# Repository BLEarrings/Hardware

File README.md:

# BLEarrings Hardware 

## Description
This repository contains the files for a custom project including a KiCad PCB design, a custom KiCad parts library, and a Blender-modeled enclosure.

## Contents
- **KiCad PCB Design (in PCB)**: The PCB design files for the project.
- **Custom KiCad Parts Library (in EasyEDA2kiCAD)**: A library of custom parts used in the PCB design.
- **Blender Modeled Enclosure (in CAD)**: 3D models of the enclosure designed in Blender.

## Getting Started
1. **Install KiCad**: Download and install KiCad from the official website.
2. **Install Blender**: Download and install Blender from the official website.
3. **Open the Project**: Open the KiCad project files in KiCad and the Blender files in Blender.

## Usage
- **KiCad PCB Design**: Use KiCad to view and modify the PCB design or checkout the [V1 Schematic](https://github.com/BLEarrings/Hardware/blob/main/PCB/Schematics/BLEEarringsV1.pdf).
- **Custom KiCad Parts Library EASYEDA2KICAD**: Use the custom parts library (easyeda2kicad) in your KiCad projects.
- **Blender Modeled Enclosure**: Use Blender to view and modify the enclosure design or use the provided STL to print one yourself.

## License
This project is licensed under the MIT License - see the `LICENSE` file for details.

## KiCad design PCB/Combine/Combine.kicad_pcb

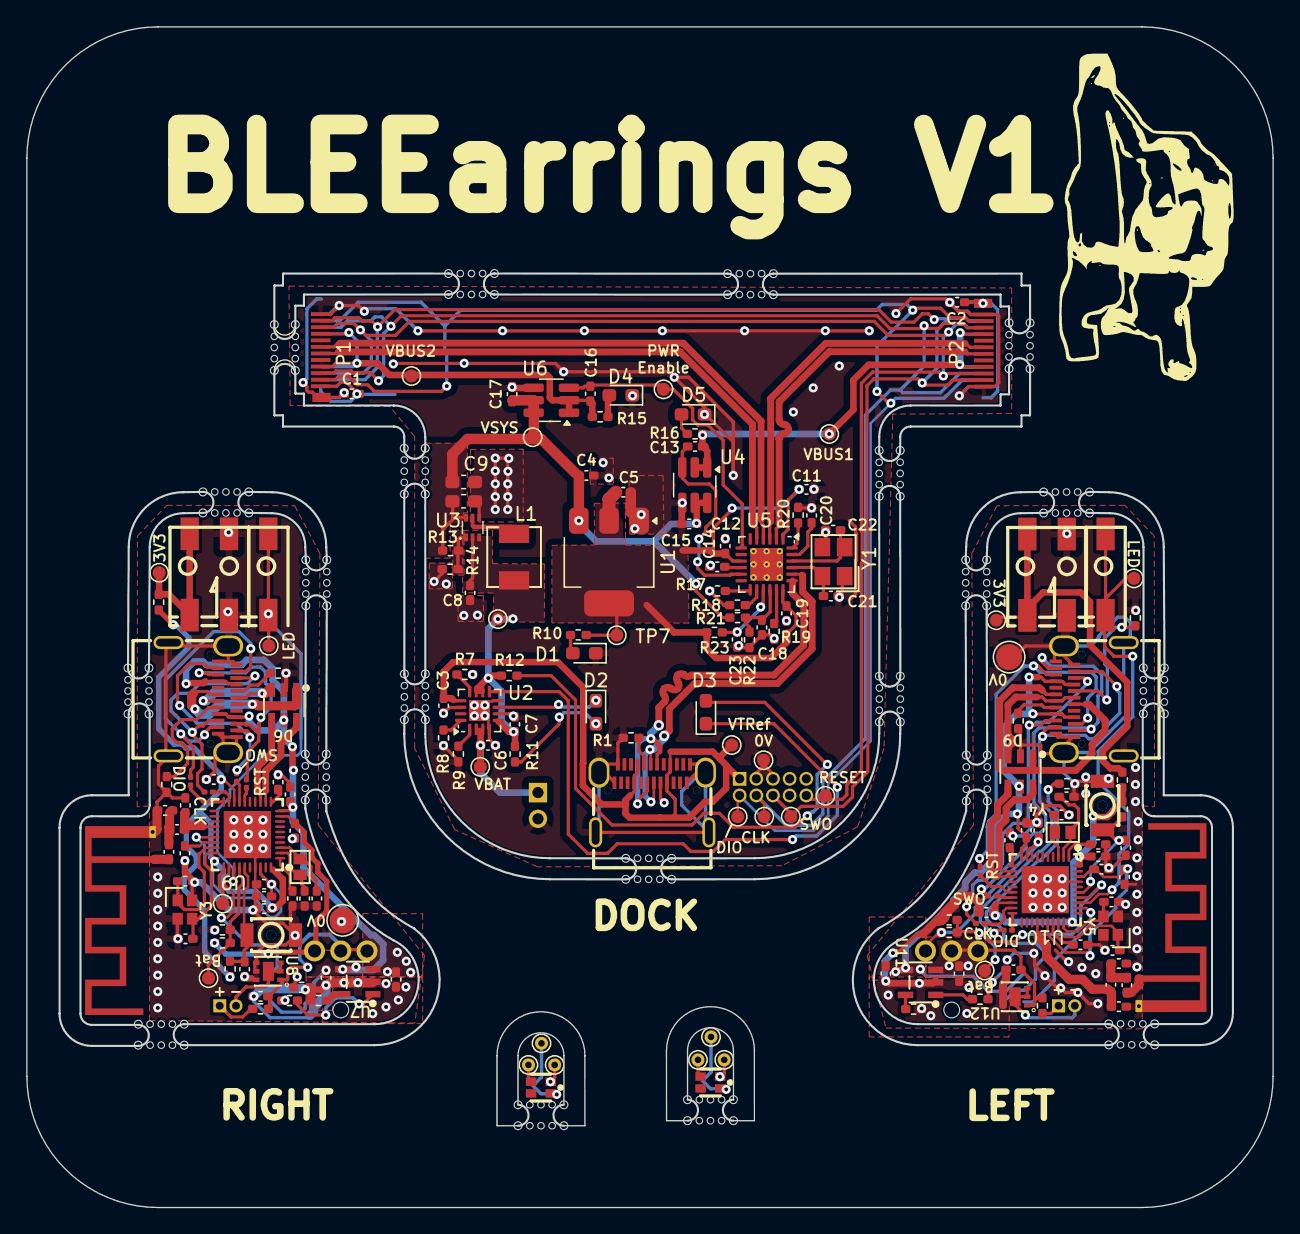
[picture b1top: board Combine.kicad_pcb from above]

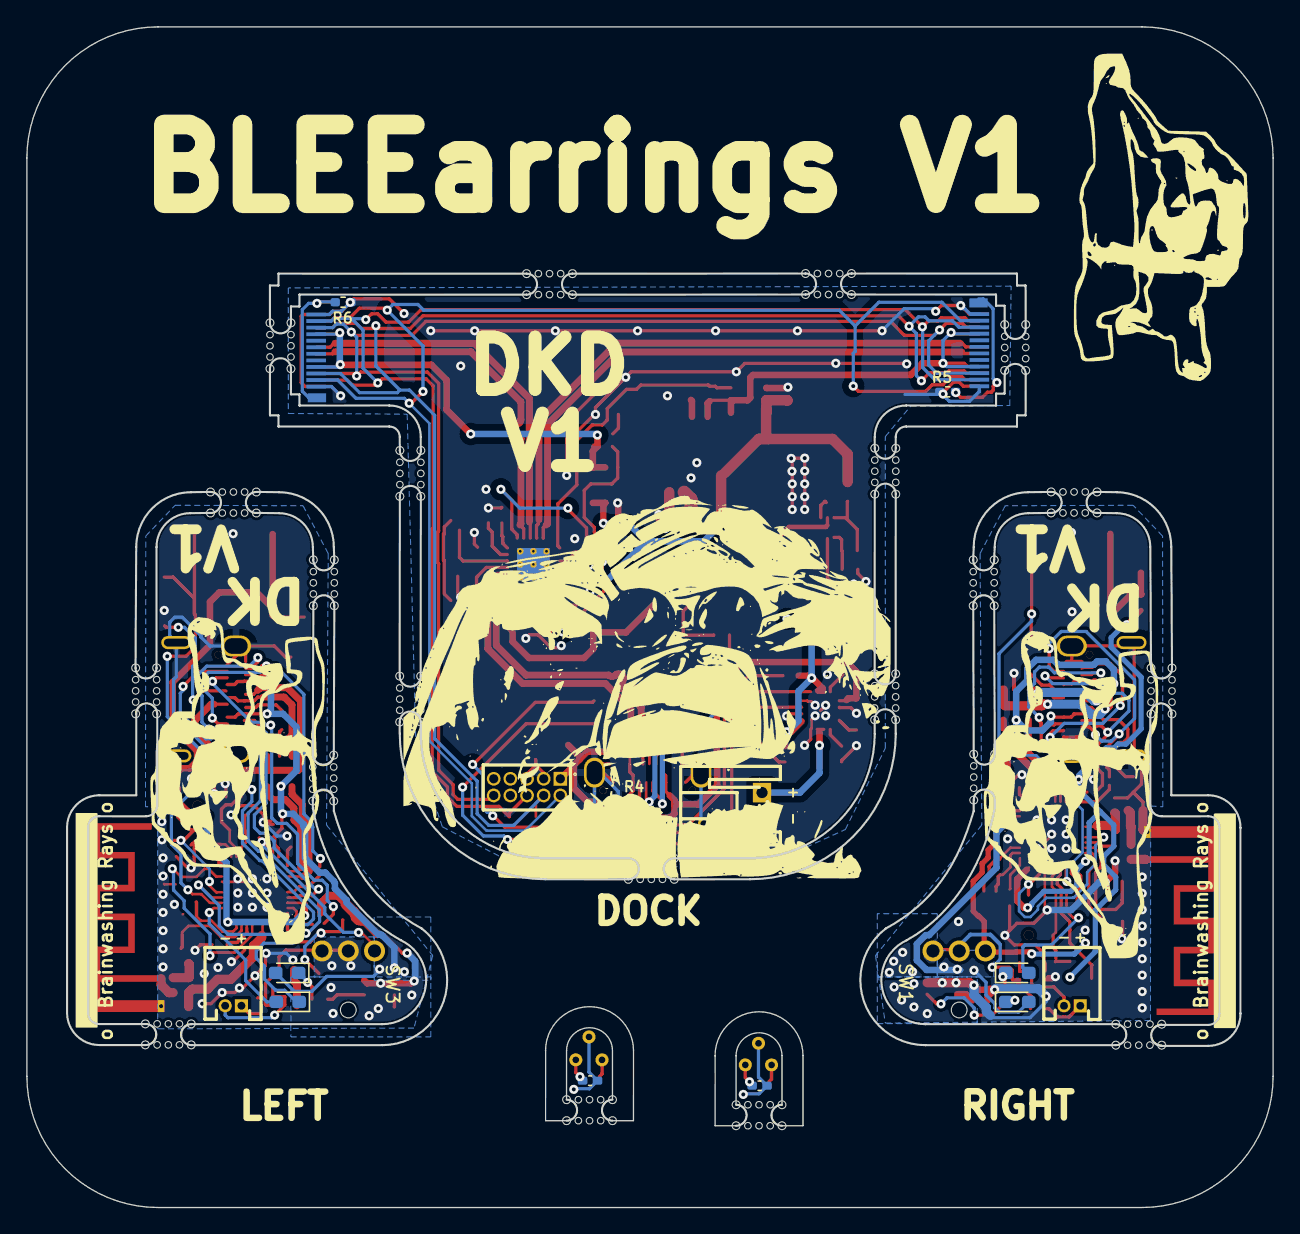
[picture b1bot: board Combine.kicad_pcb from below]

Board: 2 copper layers, 95.0 x 90.0 mm, 194 parts (15 on the bottom side), 135 nets.

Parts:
ANT1, ANT2: Texas_SWRA117D_2.4GHz_Left
BT1: Battery Pimoroni 1200mAh; CONN-TH_S2B-PH-K-S-LF-SN
BT2, BT3: Battery Gens ace 200mAh 1S 45C 3.7V; CONN-TH_530480210
C1, C2, C11, C13, C16, C18, C19, C20, C25, C30, C33, C41, C46, C49, C57, C60, C63, C64: 100n; C_0402_1005Metric_Pad0.74x0.62mm_HandSolder
C3, C12, C14, C23, C34, C38, C50, C54: 1u; C_0402_1005Metric_Pad0.74x0.62mm_HandSolder
C4, C5: 2.2u; C_0402_1005Metric_Pad0.74x0.62mm_HandSolder
C6, C7, C15, C17, C28, C29, C31, C44, C45, C47: 4.7u; C_0402_1005Metric_Pad0.74x0.62mm_HandSolder
C8, C24, C26, C59, C61: 10u; C_0402_1005Metric_Pad0.74x0.62mm_HandSolder
C9, C10: 22u; C_0603_1608Metric_Pad1.08x0.95mm_HandSolder
C21, C22: 18p; C_0402_1005Metric_Pad0.74x0.62mm_HandSolder
C27, C32, C43, C48: 8p; C_0402_1005Metric_Pad0.74x0.62mm_HandSolder
C35, C51: 1p; C_0402_1005Metric_Pad0.74x0.62mm_HandSolder
C36, C52: 100p; C_0402_1005Metric_Pad0.74x0.62mm_HandSolder
C37, C53: 1.2p; C_0402_1005Metric_Pad0.74x0.62mm_HandSolder
C39, C55: NC; C_0402_1005Metric_Pad0.74x0.62mm_HandSolder
C40, C42, C56, C58: 12p; C_0402_1005Metric_Pad0.74x0.62mm_HandSolder
D1: LED; LED_0603_1608Metric_Pad1.05x0.95mm_HandSolder
D2: BLUE RED; LED_0603_1608Metric_Pad1.05x0.95mm_HandSolder
D3, D4, D5, D8, D10: BLUE LED; LED_0603_1608Metric_Pad1.05x0.95mm_HandSolder
D6, D9: USBLC6-2SC6_C2687116; SOT-23-6_L2.9-W1.6-P0.95-LS2.8-BL
D7, D11: RED LED; LED_0603_1608Metric_Pad1.05x0.95mm_HandSolder
D12, D13: 2758; LED-SMD_4P-L1.6-W1.5_XL-1615RGBC-WS2812B
J1, J3, J6: USB_C_Receptacle; TYPE-C-SMD_C9900025773
J2: Conn_01x10_Socket; HDR-TH_10P-P1.27-V-M-R2-C5-S1.27-1
J4, J7: Screw_Terminal_01x01; CONN-SMD_custom1
J5, J8: Screw_Terminal_01x02; CONN-SMD_2059-302
L1: 4.7u; IND-SMD_L4.5-W4.1
L2, L4: 4.7n; L_0402_1005Metric_Pad0.77x0.64mm_HandSolder
L3, L5: 2.2n; L_0402_1005Metric_Pad0.77x0.64mm_HandSolder
P1, P2: USB_C_Plug; USB-C-SMD_TYPE-C-24P-GTJB-040
R1, R4, R24, R25, R38, R39: 5k1; R_0402_1005Metric_Pad0.72x0.64mm_HandSolder
R5, R6, R11, R12: 1k; R_0402_1005Metric_Pad0.72x0.64mm_HandSolder
R7: 1.18k; R_0402_1005Metric_Pad0.72x0.64mm_HandSolder
R8: 1.78k; R_0402_1005Metric_Pad0.72x0.64mm_HandSolder
R9, R21, R22, R23: 10k; R_0402_1005Metric_Pad0.72x0.64mm_HandSolder
R10, R26, R37, R48, R49: 2k; R_0402_1005Metric_Pad0.72x0.64mm_HandSolder
R13: 732; R_0402_1005Metric_Pad0.72x0.64mm_HandSolder
R14, R34, R45: 100k; R_0402_1005Metric_Pad0.72x0.64mm_HandSolder
R15, R16, R29, R40: 220; R_0402_1005Metric_Pad0.72x0.64mm_HandSolder
R17, R18, R19, R28, R51: 100; R_0402_1005Metric_Pad0.72x0.64mm_HandSolder
R20: 12k; R_0402_1005Metric_Pad0.72x0.64mm_HandSolder
R27, R50: 4k99; R_0402_1005Metric_Pad0.72x0.64mm_HandSolder
R30, R31, R32, R33, R41, R42, R43, R44: NF; R_0201_0603Metric
R35, R46: 33k; R_0402_1005Metric_Pad0.72x0.64mm_HandSolder
R36, R47: 470; R_0402_1005Metric_Pad0.72x0.64mm_HandSolder
SW1, SW3: TK-6580B-1; SW-TH_TK-6580B-1
SW2, SW4: SW_DIP_x01; KEY-SMD_L3.0-W2.5-LS4.0
TP1, TP2, TP3, TP4, TP5, TP6, TP7, TP8, TP9, TP10, TP11, TP12, TP13, TP14, TP15, TP17, TP18, TP19, TP28: TestPoint; TestPoint_Pad_D1.0mm
TP16, TP20: TestPoint; TestPoint_Pad_D2.0mm
TP21, TP22, TP23, TP24, TP25, TP26: TestPoint; TestPoint_THTPad_D1.0mm_Drill0.5mm
TPL3: TestPoint; TestPoint_Pad_D1.0mm
U1: AMS1117-3.3; SOT-223-3_TabPin2
U2: BQ24073RGT; VQFN-16-1EP_3x3mm_P0.5mm_EP1.6x1.6mm
U3: TPS61023DRLR; SOT-563_L1.6-W1.2-P0.50-LS1.6-BR
U4, U6: SIP32509DT-T1-GE3; SOT-23-6_Handsoldering
U5: USB2422T-I/MJ; HVQFN-24-1EP_4x4mm_P0.5mm_EP2.5x2.5mm_ThermalVias
U7, U11: MCP73831T-2ACI/OT; SOT-23-5_L3.0-W1.7-P0.95-LS2.8-BL
U8, U12: XB6096I2SV; WDFN-6_L2.0-W2.0-P0.65-BL-EP
U9, U10: NRF52833-QDAA-R7; QFN-40_L5.0-W5.0-P0.40-TL-EP3.6
Y1: X322524MOB4SI; CRYSTAL-SMD_4P-L3.2-W2.5-BL
Y2, Y4: X161032768KLD2SI; CRYSTAL-SMD_L1.6-W1.0
Y3, Y5: XL7EL89CKI-111YLC-32M; CRYSTAL-SMD_4P-L2.0-W1.6-BL

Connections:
+3V3_1: C5.1, C11.2, C12.2, C19.2, R10.2, R23.2, TP7.1, U1.2 (VO), U5.1 (VDD33), U5.9 (VDD33), U5.18 (VDD33)
+3V3_2: C30.1, C34.2, R36.2, R37.2, U9.18 (VDD), U9.30 (VDD), U9.40 (VDD)
+3V3_3: C46.1, C50.2, R47.2, R48.2, U10.18 (VDD), U10.30 (VDD), U10.40 (VDD)
+BATT_1: C28.2, R34.2, SW1.3, U9.9 (VDDH)
+BATT_2: C44.2, R45.2, SW3.3, U10.9 (VDDH)
/Dock/DeviceSelect/D+: J1.A6 (D+), J1.B6 (D+), U5.20 (USBDP_UP)
/Dock/DeviceSelect/D-: J1.A7 (D-), J1.B7 (D-), U5.19 (USBDM_UP)
/Dock/DeviceSelect/D_1+: P2.A6 (D+), U5.3 (USBDP_DN1/PRT_DIS_P1)
/Dock/DeviceSelect/D_1-: P2.A7 (D-), U5.2 (USBDM_DN1/PRT_DIS_M1)
/Dock/DeviceSelect/D_2+: P1.A6 (D+), U5.5 (USBDP_DN2/PRT_DIS_P2)
/Dock/DeviceSelect/D_2-: P1.A7 (D-), U5.4 (USBDM_DN2/PRT_DIS_M2)
/Dock/DeviceSelect/VBUS1: C13.2, P2.A4 (VBUS), P2.A9 (VBUS), P2.B4 (VBUS), P2.B9 (VBUS), R16.1, TP11.1, U4.1 (OUT), U4.2 (OUT)
/Dock/DeviceSelect/VBUS2: C16.2, P1.A4 (VBUS), P1.A9 (VBUS), P1.B4 (VBUS), P1.B9 (VBUS), R15.1, TP12.1, U6.1 (OUT), U6.2 (OUT)
/Dock/DeviceSelect/Vsys: C4.1, C9.1, C10.1, C15.2, C17.2, R13.2, R21.2, TP10.1, U1.3 (VI), U3.6 (VOUT), U4.5 (IN), U4.6 (IN), U6.5 (IN), U6.6 (IN)
/Dock/ExtraBattery/3.7Out: C7.1, C8.1, L1.1, R11.2, R12.2, TP9.1, U2.5 (EN2), U2.10 (OUT), U2.11 (OUT), U3.2 (EN), U3.3 (VIN)
/Dock/ExtraBattery/FB: R13.1, R14.2, U3.1 (FB)
/Dock/ExtraBattery/VBAT: BT1.1 (+), C6.1, TP8.1, U2.2 (BAT), U2.3 (BAT)
/EarringL/DSP/VBUS: C45.2, C61.1, D9.5 (VBUS), D11.2 (A), J6.A4 (VBUS), U10.10 (VBUS), U11.4 (VDD)
/EarringL/DSP/nReset: J6.A10 (RX2-), J6.B10 (RX1-), R43.1
/EarringL/LUSBd+: D9.3 (I/O2), J6.A6 (D+), J6.B6 (D+)
/EarringL/LUSBd-: D9.1 (I/O1), J6.A7 (D-), J6.B7 (D-)
/EarringL/Power/VBAT: C59.1, C60.1, R51.2, SW3.1, SW3.2, U11.3 (VBAT), U12.1 (VDD)
/EarringR/DSP/VBUS: C26.1, C29.2, D6.5 (VBUS), D7.2 (A), J3.A4 (VBUS), U7.4 (VDD), U9.10 (VBUS)
/EarringR/DSP/nReset: J3.A10 (RX2-), J3.B10 (RX1-), R32.1
/EarringR/Power/VBAT: C24.1, C25.1, R28.2, SW1.1, SW1.2, U7.3 (VBAT), U8.1 (VDD)
BatRef_1: R34.1, R35.2, TP13.1, U9.34 (P0.29_AIN5)
BatRef_2: R45.1, R46.2, TP17.1, U10.34 (P0.29_AIN5)
D1+: D6.4 (I/O2), U9.13 (D+)
D1-: D6.6 (I/O1), U9.12 (D-)
D2+: D9.4 (I/O2), U10.13 (D+)
D2-: D9.6 (I/O1), U10.12 (D-)
DEC6_1: C38.1, C39.1, U9.26 (DEC6), U9.38 (DEC4)
DEC6_2: C54.1, C55.1, U10.26 (DEC6), U10.38 (DEC4)
GND1: BT1.2 (-), C1.1, C2.1, C3.2, C4.2, C5.2, C6.2, C7.2, C8.2, C9.2, C10.2, C11.1, C12.1, C14.1, C15.1, C17.1, C18.1, C19.1, C20.1, C21.2, C22.1, C23.1, D1.1 (K), D4.1 (K), D5.1 (K), J1.A1 (GND), J1.S1 (SHIELD), J2.3, J2.5, P1.A1 (GND), P2.A1 (GND), R1.1, R4.1, R5.2, R6.2, R7.2, R8.2, R9.1, R14.1, R17.1, R18.1, R19.1, R20.1, R22.1, TP1.1, U1.1 (GND), U2.4 (~CE), U2.6 (EN1), U2.8 (VSS), U2.14 (TMR), U2.17 (VSS), U3.4 (GND), U4.4 (GND), U5.25 (EP), U6.4 (GND), Y1.1, Y1.3
GND2: ANT1.2 (GND), C24.2, C25.2, C26.2, C27.1, C28.1, C29.1, C30.2, C31.1, C32.1, C33.1, C34.1, C35.2, C36.2, C37.2, C38.2, C39.2, C40.1, C41.1, C42.1, D6.2 (GND), J3.A1 (GND), J3.S1 (SHIELD), J5.2, R24.1, R25.1, R27.2, R29.1, R35.1, SW2.2, TP16.1, U7.2 (VSS), U8.4 (VM), U8.5 (VM), U8.6 (VM), U9.37 (VSS), U9.41 (VSS), Y3.2, Y3.3
GND3: ANT2.2 (GND), C43.1, C44.1, C45.1, C46.2, C47.1, C48.1, C49.1, C50.1, C51.2, C52.2, C53.2, C54.2, C55.2, C56.1, C57.1, C58.1, C59.2, C60.2, C61.2, D9.2 (GND), J6.A1 (GND), J6.S1 (SHIELD), J8.2, R38.1, R39.1, R40.1, R46.1, R50.2, SW4.2, TP20.1, U10.37 (VSS), U10.41 (VSS), U11.2 (VSS), U12.4 (VM), U12.5 (VM), U12.6 (VM), Y5.2, Y5.3
LED_A_1: D8.2 (A), U9.32 (P0.02_AIN0)
LED_A_2: D10.2 (A), U10.32 (P0.02_AIN0)
NEO_LED_1: J4.1, TP14.1, U9.33 (P0.28_AIN4)
NEO_LED_2: J7.1, TP18.1, U10.33 (P0.28_AIN4)
unnamed: ANT1.1 (FP), L3.2
unnamed: ANT2.1 (FP), L5.2
unnamed: BT2.1 (+), R28.1
unnamed: BT2.2 (-), U8.2 (GND), U8.3 (GND), U8.7 (EP)
unnamed: BT3.1 (+), R51.1
unnamed: BT3.2 (-), U12.2 (GND), U12.3 (GND), U12.7 (EP)
unnamed: C37.1, L2.2, L3.1
unnamed: C53.1, L4.2, L5.1
unnamed: D1.2 (A), R10.1
unnamed: D2.2 (A), R11.1
unnamed: D2.1 (K), U2.7 (~PGOOD)
unnamed: D3.2 (A), R12.1
unnamed: D3.1 (K), U2.9 (~CHG)
unnamed: D4.2 (A), R15.2
unnamed: D5.2 (A), R16.2
unnamed: D6.1 (I/O1), J3.A7 (D-), J3.B7 (D-)
unnamed: D6.3 (I/O2), J3.A6 (D+), J3.B6 (D+)
unnamed: D7.1 (K), R26.1
unnamed: D8.1 (K), R29.2
unnamed: D10.1 (K), R40.2
unnamed: D11.1 (K), R49.1
unnamed: D12.4 (DIN), TP21.1
unnamed: C63.2, D12.1 (VDD), TP22.1
unnamed: C63.1, D12.3 (VSS), TP23.1
unnamed: D13.4 (DIN), TP24.1
unnamed: C64.2, D13.1 (VDD), TP25.1
unnamed: C64.1, D13.3 (VSS), TP26.1
unnamed: J1.A5 (CC1), R1.2
unnamed: J1.B5 (CC2), R4.2
unnamed: J3.A5 (CC1), R24.2
unnamed: J3.B5 (CC2), R25.2
unnamed: J5.1, R36.1, TP15.1
unnamed: J6.A5 (CC1), R38.2
unnamed: J6.B5 (CC2), R39.2
unnamed: J8.1, R47.1, TP19.1
unnamed: C1.2, P1.S1 (SHIELD), R5.1
unnamed: C2.2, P2.S1 (SHIELD), R6.1
unnamed: R7.1, U2.12 (ILIM)
unnamed: R8.1, U2.16 (ISET)
unnamed: R9.2, U2.1 (TS)
unnamed: L1.2, U3.5 (SW)
unnamed: C14.2, U5.10 (CRFILT)
unnamed: C20.2, U5.23 (PLLFILT)
unnamed: R20.2, U5.24 (RBIAS)
unnamed: R18.2, U5.14 (SMBCLK/CFG_SEL0)
unnamed: R17.2, U5.13 (SMBDATA/NON_REM1)
unnamed: R19.2, U5.17 (SUSP_IND/LOCAL_PWR/(NON_REM0))
unnamed: C18.2, R21.1, R22.2, U5.16 (VBUS_DET)
unnamed: C22.2, U5.22 (XTALIN/CLKIN), Y1.2
unnamed: C21.1, U5.21 (XTALOUT/(CLKIN_EN)), Y1.4
unnamed: R27.1, U7.5 (PROG)
unnamed: R26.2, U7.1 (STAT)
unnamed: C35.1, L2.1, U9.24 (ANT)
unnamed: C33.2, U9.1 (DEC1)
unnamed: C36.1, U9.27 (DEC3)
unnamed: C31.2, U9.11 (DECUSB)
unnamed: C27.2, U9.2 (P0.00_XL1), Y2.2
unnamed: C32.2, U9.3 (P0.01_XL2), Y2.1
unnamed: TPL3.1, U9.31 (P0.03_AIN1)
unnamed: R32.2, U9.16 (P0.18_nRESET)
unnamed: R30.1, U9.17 (P0.20)
unnamed: R31.1, U9.20 (SWDCLK)
unnamed: R33.2, U9.19 (SWDIO)
unnamed: C42.2, U9.28 (XC1), Y3.1
unnamed: C40.2, U9.29 (XC2), Y3.4
unnamed: C51.1, L4.1, U10.24 (ANT)
unnamed: C49.2, U10.1 (DEC1)
unnamed: C52.1, U10.27 (DEC3)
unnamed: C47.2, U10.11 (DECUSB)
unnamed: C43.2, U10.2 (P0.00_XL1), Y4.2
unnamed: C48.2, U10.3 (P0.01_XL2), Y4.1
unnamed: R43.2, U10.16 (P0.18_nRESET)
unnamed: R41.1, U10.17 (P0.20)
unnamed: R42.1, U10.20 (SWDCLK)
unnamed: R44.2, U10.19 (SWDIO)
unnamed: C58.2, U10.28 (XC1), Y5.1
unnamed: C56.2, U10.29 (XC2), Y5.4
unnamed: R50.1, U11.5 (PROG)
unnamed: R49.2, U11.1 (STAT)
PWREN1: C13.1, U4.3 (EN), U5.11 (PRTPWR2)
PWREN2: C16.1, TP28.1, U5.7 (PRTPWR1/(BC_EN1)), U6.3 (EN)
Pair_1: C41.2, R37.1, SW2.1, U9.35 (P0.30_AIN6)
Pair_2: C57.2, R48.1, SW4.1, U10.35 (P0.30_AIN6)
RESET: C23.2, R23.1, U5.15 (RESET_N)
SWCLK: J2.4, P1.A3 (TX1-), P1.B3 (TX2-), P2.A3 (TX1-), P2.B3 (TX2-), TP2.1
SWDCLK_L_1: J3.A3 (TX1-), J3.B3 (TX2-), R33.1
SWDCLK_L_2: J6.A3 (TX1-), J6.B3 (TX2-), R44.1
SWDIO: J2.2, P1.A2 (TX1+), P1.B2 (TX2+), P2.A2 (TX1+), P2.B2 (TX2+), TP6.1
SWDIO_L_1: J3.A2 (TX1+), J3.B2 (TX2+), R31.2
SWDIO_L_2: J6.A2 (TX1+), J6.B2 (TX2+), R42.2
SWO: J2.6, P1.A11 (RX2+), P1.B11 (RX1+), P2.A11 (RX2+), P2.B11 (RX1+), TP5.1
SWO_L_1: J3.A11 (RX2+), J3.B11 (RX1+), R30.2
SWO_L_2: J6.A11 (RX2+), J6.B11 (RX1+), R41.2
VTRef: C3.1, J1.A4 (VBUS), J2.1, TP3.1, U2.13 (IN)
nRESET: J2.10, P1.A10 (RX2-), P1.B10 (RX1-), P2.A10 (RX2-), P2.B10 (RX1-), TP4.1

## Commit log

2024-12-26 PCB P1
2024-12-27 Adding some renders
2025-01-13 Blender file of PCB made
2025-01-13 Adding in a WIP modelling file
2025-01-14 Split up for STLs
